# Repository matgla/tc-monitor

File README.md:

# tc-monitor

Four-channel thermocouple monitor for hand reflow with hot air and a preheater:
live temperature and graph on a 2.0" colour TFT, phase hints (preheat, soak, hot air,
liquid, cooling), peak-limit and ramp alarms, CSV over USB.

| directory | contents |
|---|---|
| `docs/design.md` | requirements, parts, RP2040 pin map, layout rules |
| `hardware/` | KiCad 10 project: schematic (5 sheets, ERC without errors); `libs/` holds the PCC-SMP footprint and the crystal symbol |
| `firmware/` | MicroPython: `reflow.py` (phase logic), `config.py`, `main.py` (still for the prototype's MAX31856/SH1106, to be ported) |
| `host/tc_plot.py` | live plot over USB, saves every run as CSV |
| `tests/` | pytest for the phase logic |

```sh
python -m pytest -q tests
uv run --with pyserial --with pyqtgraph --with PySide6 host/tc_plot.py
```

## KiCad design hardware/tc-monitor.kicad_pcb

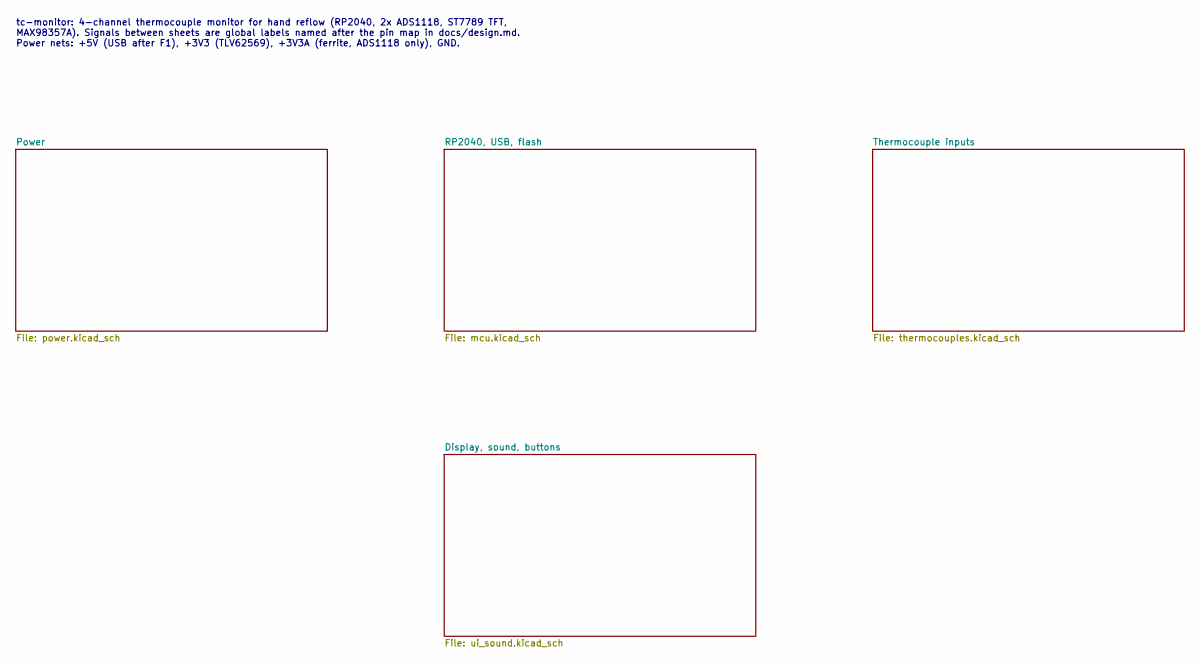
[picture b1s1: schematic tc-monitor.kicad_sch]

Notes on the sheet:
tc-monitor: 4-channel thermocouple monitor for hand reflow (RP2040, 2x ADS1118, ST7789 TFT, MAX98357A). Signals between sheets are global labels named after the pin map in docs/design.md. Power nets: +5V (USB after F1), +3V3 (TLV62569), +3V3A (ferrite, ADS1118 only), GND.

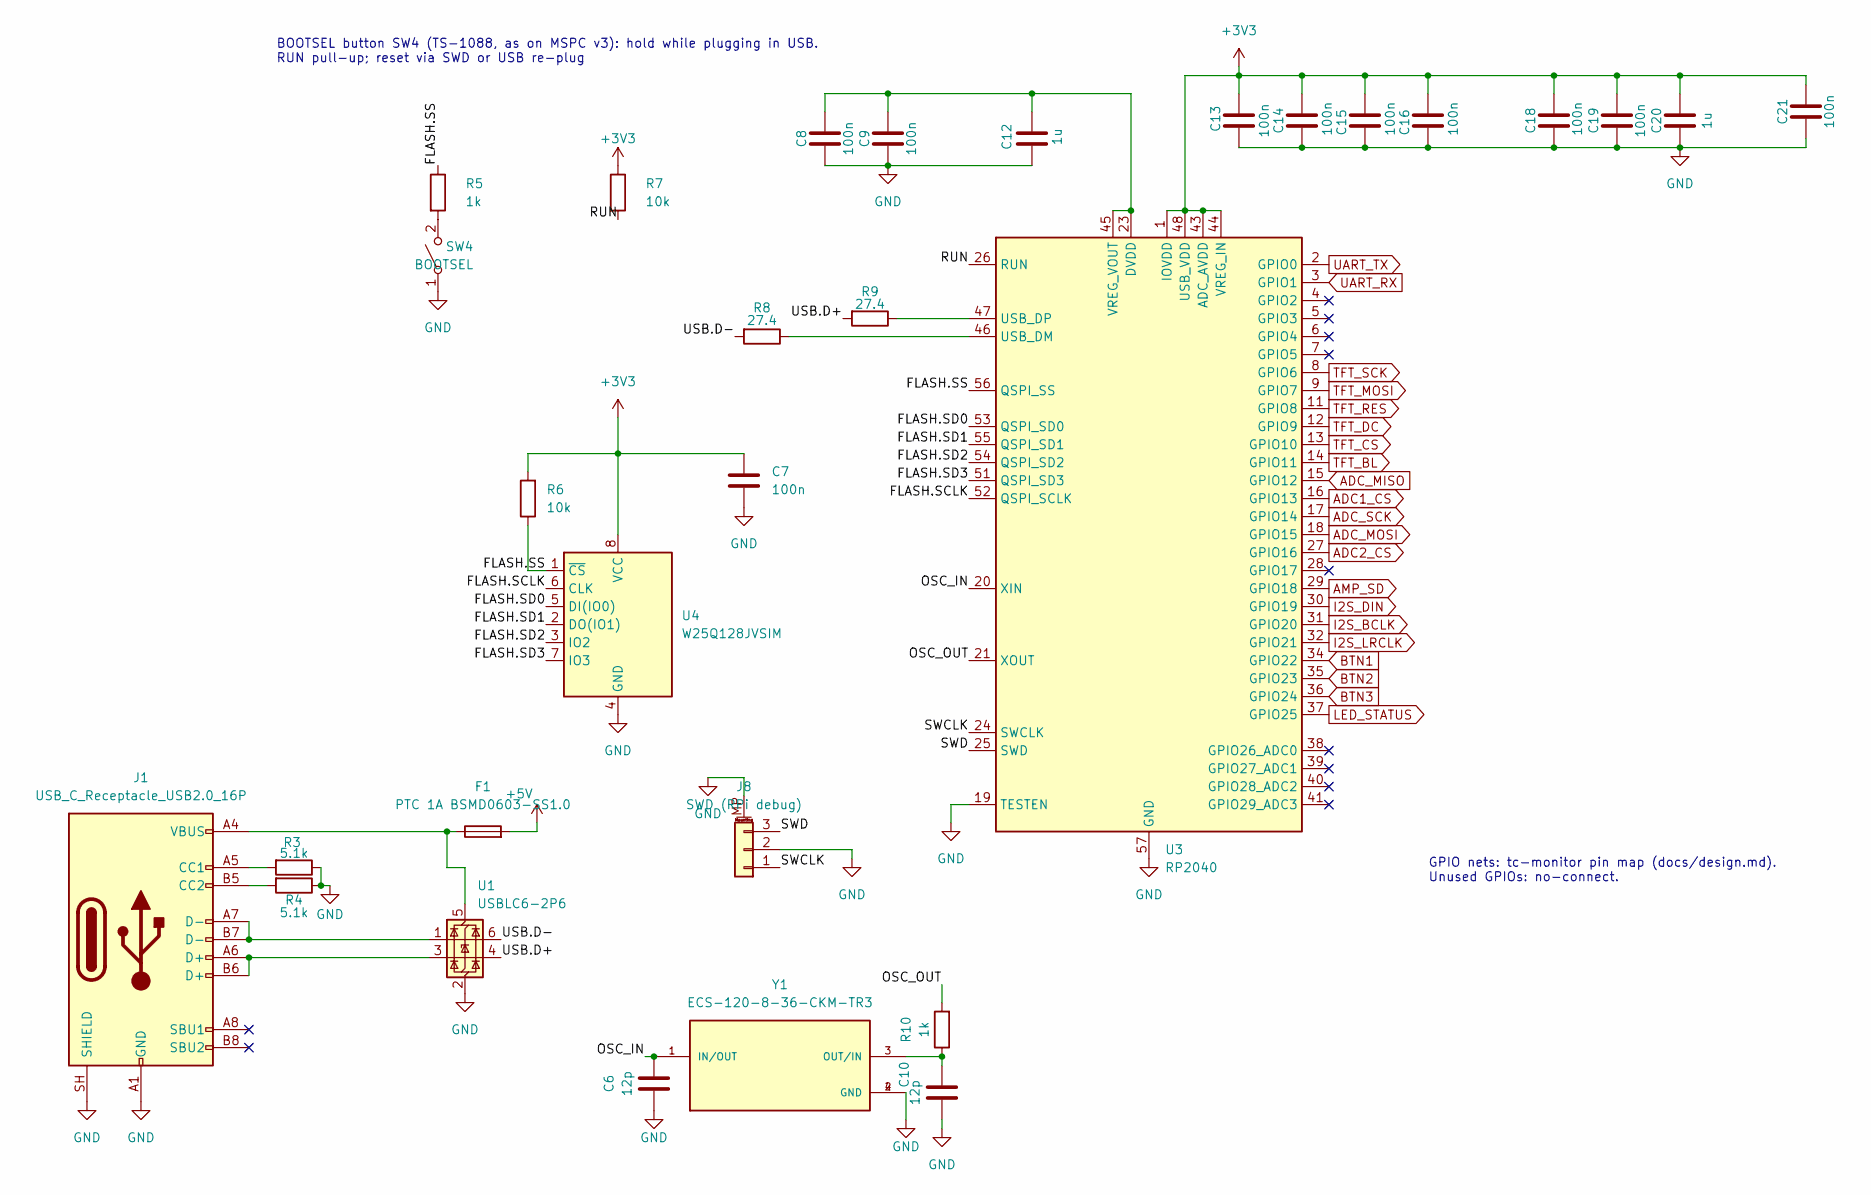
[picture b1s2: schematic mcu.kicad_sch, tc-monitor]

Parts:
C6, C10: 12p; C_0402_1005Metric_Pad0.74x0.62mm_HandSolder
C7, C8, C9, C13, C14, C15, C16, C18, C19, C21: 100n; C_0402_1005Metric_Pad0.74x0.62mm_HandSolder
C12, C20: 1u; C_0402_1005Metric_Pad0.74x0.62mm_HandSolder
F1: PTC 1A BSMD0603-SS1.0; Fuse_0603_1608Metric_Pad1.05x0.95mm_HandSolder
J1: USB_C_Receptacle_USB2.0_16P; USB_C_Receptacle_HRO_TYPE-C-31-M-12
J8: SWD (RPi debug); JST_SH_BM03B-SRSS-TB_1x03-1MP_P1.00mm_Vertical; MPN BM03B-SRSS-TB(LF)(SN); LCSC C160389
R3, R4: 5.1k; R_0402_1005Metric_Pad0.72x0.64mm_HandSolder
R5, R10: 1k; R_0402_1005Metric_Pad0.72x0.64mm_HandSolder
R6, R7: 10k; R_0402_1005Metric_Pad0.72x0.64mm_HandSolder
R8, R9: 27.4; R_0402_1005Metric_Pad0.72x0.64mm_HandSolder
SW4: BOOTSEL; SW_SPST_TS-1088-xR020; MPN TS-1088-AR02016; LCSC C720477
U1: USBLC6-2P6; SOT-666
U3: RP2040; QFN-56-1EP_7x7mm_P0.4mm_EP3.2x3.2mm_ThermalVias_D0.3
U4: W25Q128JVSIM; SOIC-8_5.3x5.3mm_P1.27mm; MPN GD25Q16EEIGR; LCSC C2986331
Y1: ECS-120-8-36-CKM-TR3; Crystal_SMD_2520-4Pin_2.5x2.0mm; PARTREV 2017; LCSC C20625731

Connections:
+3V3: C7.1, C13.1, C14.1, C15.1, C16.1, C18.1, C19.1, C20.1, C21.1, R6.2, R7.1, U3.1 (IOVDD), U3.10 (IOVDD), U3.22 (IOVDD), U3.33 (IOVDD), U3.42 (IOVDD), U3.43 (ADC_AVDD), U3.44 (VREG_IN), U3.48 (USB_VDD), U3.49 (IOVDD), U4.8 (VCC); also elsewhere on the board
+5V: F1.2; also elsewhere on the board
/RP2040, USB, flash/FLASH.SCLK: U3.52 (QSPI_SCLK), U4.6 (CLK)
/RP2040, USB, flash/FLASH.SD0: U3.53 (QSPI_SD0), U4.5 (DI(IO0))
/RP2040, USB, flash/FLASH.SD1: U3.55 (QSPI_SD1), U4.2 (DO(IO1))
/RP2040, USB, flash/FLASH.SD2: U3.54 (QSPI_SD2), U4.3 (IO2)
/RP2040, USB, flash/FLASH.SD3: U3.51 (QSPI_SD3), U4.7 (IO3)
/RP2040, USB, flash/FLASH.SS: R5.1, R6.1, U3.56 (QSPI_SS), U4.1 (~CS)
/RP2040, USB, flash/OSC_IN: C6.1, U3.20 (XIN), Y1.1 (IN/OUT)
/RP2040, USB, flash/OSC_OUT: R10.2, U3.21 (XOUT)
/RP2040, USB, flash/RUN: R7.2, U3.26 (RUN)
/RP2040, USB, flash/SWCLK: J8.1, U3.24 (SWCLK)
/RP2040, USB, flash/SWD: J8.3, U3.25 (SWD)
/RP2040, USB, flash/USB.D+: R9.2, U1.4 (I/O2)
/RP2040, USB, flash/USB.D-: R8.2, U1.6 (I/O1)
ADC1_CS: U3.16 (GPIO13); also elsewhere on the board
ADC2_CS: U3.27 (GPIO16); also elsewhere on the board
ADC_MISO: U3.15 (GPIO12); also elsewhere on the board
ADC_MOSI: U3.18 (GPIO15); also elsewhere on the board
ADC_SCK: U3.17 (GPIO14); also elsewhere on the board
AMP_SD: U3.29 (GPIO18); also elsewhere on the board
BTN1: U3.34 (GPIO22); also elsewhere on the board
BTN2: U3.35 (GPIO23); also elsewhere on the board
BTN3: U3.36 (GPIO24); also elsewhere on the board
GND: C6.2, C7.2, C8.2, C9.2, C10.2, C12.2, C13.2, C14.2, C15.2, C16.2, C18.2, C19.2, C20.2, C21.2, J1.A1 (GND), J1.A12 (GND), J1.B1 (GND), J1.B12 (GND), J1.SH (SHIELD), J8.2, J8.MP (MountPin), R3.1, R4.1, SW4.1 (A), U1.2 (GND), U3.19 (TESTEN), U3.57 (GND), U4.4 (GND), Y1.2 (GND), Y1.4 (GND); also elsewhere on the board
I2S_BCLK: U3.31 (GPIO20); also elsewhere on the board
I2S_DIN: U3.30 (GPIO19); also elsewhere on the board
I2S_LRCLK: U3.32 (GPIO21); also elsewhere on the board
LED_STATUS: U3.37 (GPIO25); also elsewhere on the board
unnamed: J1.A5 (CC1), R3.2
unnamed: J1.B5 (CC2), R4.2
unnamed: J1.A6 (D+), J1.B6 (D+), U1.3 (I/O2)
unnamed: J1.A7 (D-), J1.B7 (D-), U1.1 (I/O1)
unnamed: R5.2, SW4.2 (B)
unnamed: F1.1, J1.A4 (VBUS), J1.A9 (VBUS), J1.B4 (VBUS), J1.B9 (VBUS), U1.5 (VBUS)
unnamed: R8.1, U3.46 (USB_DM)
unnamed: R9.1, U3.47 (USB_DP)
unnamed: C8.1, C9.1, C12.1, U3.23 (DVDD), U3.45 (VREG_VOUT), U3.50 (DVDD)
unnamed: C10.1, R10.1, Y1.3 (OUT/IN)
TFT_BL: U3.14 (GPIO11); also elsewhere on the board
TFT_CS: U3.13 (GPIO10); also elsewhere on the board
TFT_DC: U3.12 (GPIO9); also elsewhere on the board
TFT_MOSI: U3.9 (GPIO7); also elsewhere on the board
TFT_RES: U3.11 (GPIO8); also elsewhere on the board
TFT_SCK: U3.8 (GPIO6); also elsewhere on the board
UART_RX: U3.3 (GPIO1); also elsewhere on the board
UART_TX: U3.2 (GPIO0); also elsewhere on the board

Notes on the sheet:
GPIO nets: tc-monitor pin map (docs/design.md). Unused GPIOs: no-connect.
BOOTSEL button SW4 (TS-1088, as on MSPC v3): hold while plugging in USB. RUN pull-up; reset via SWD or USB re-plug

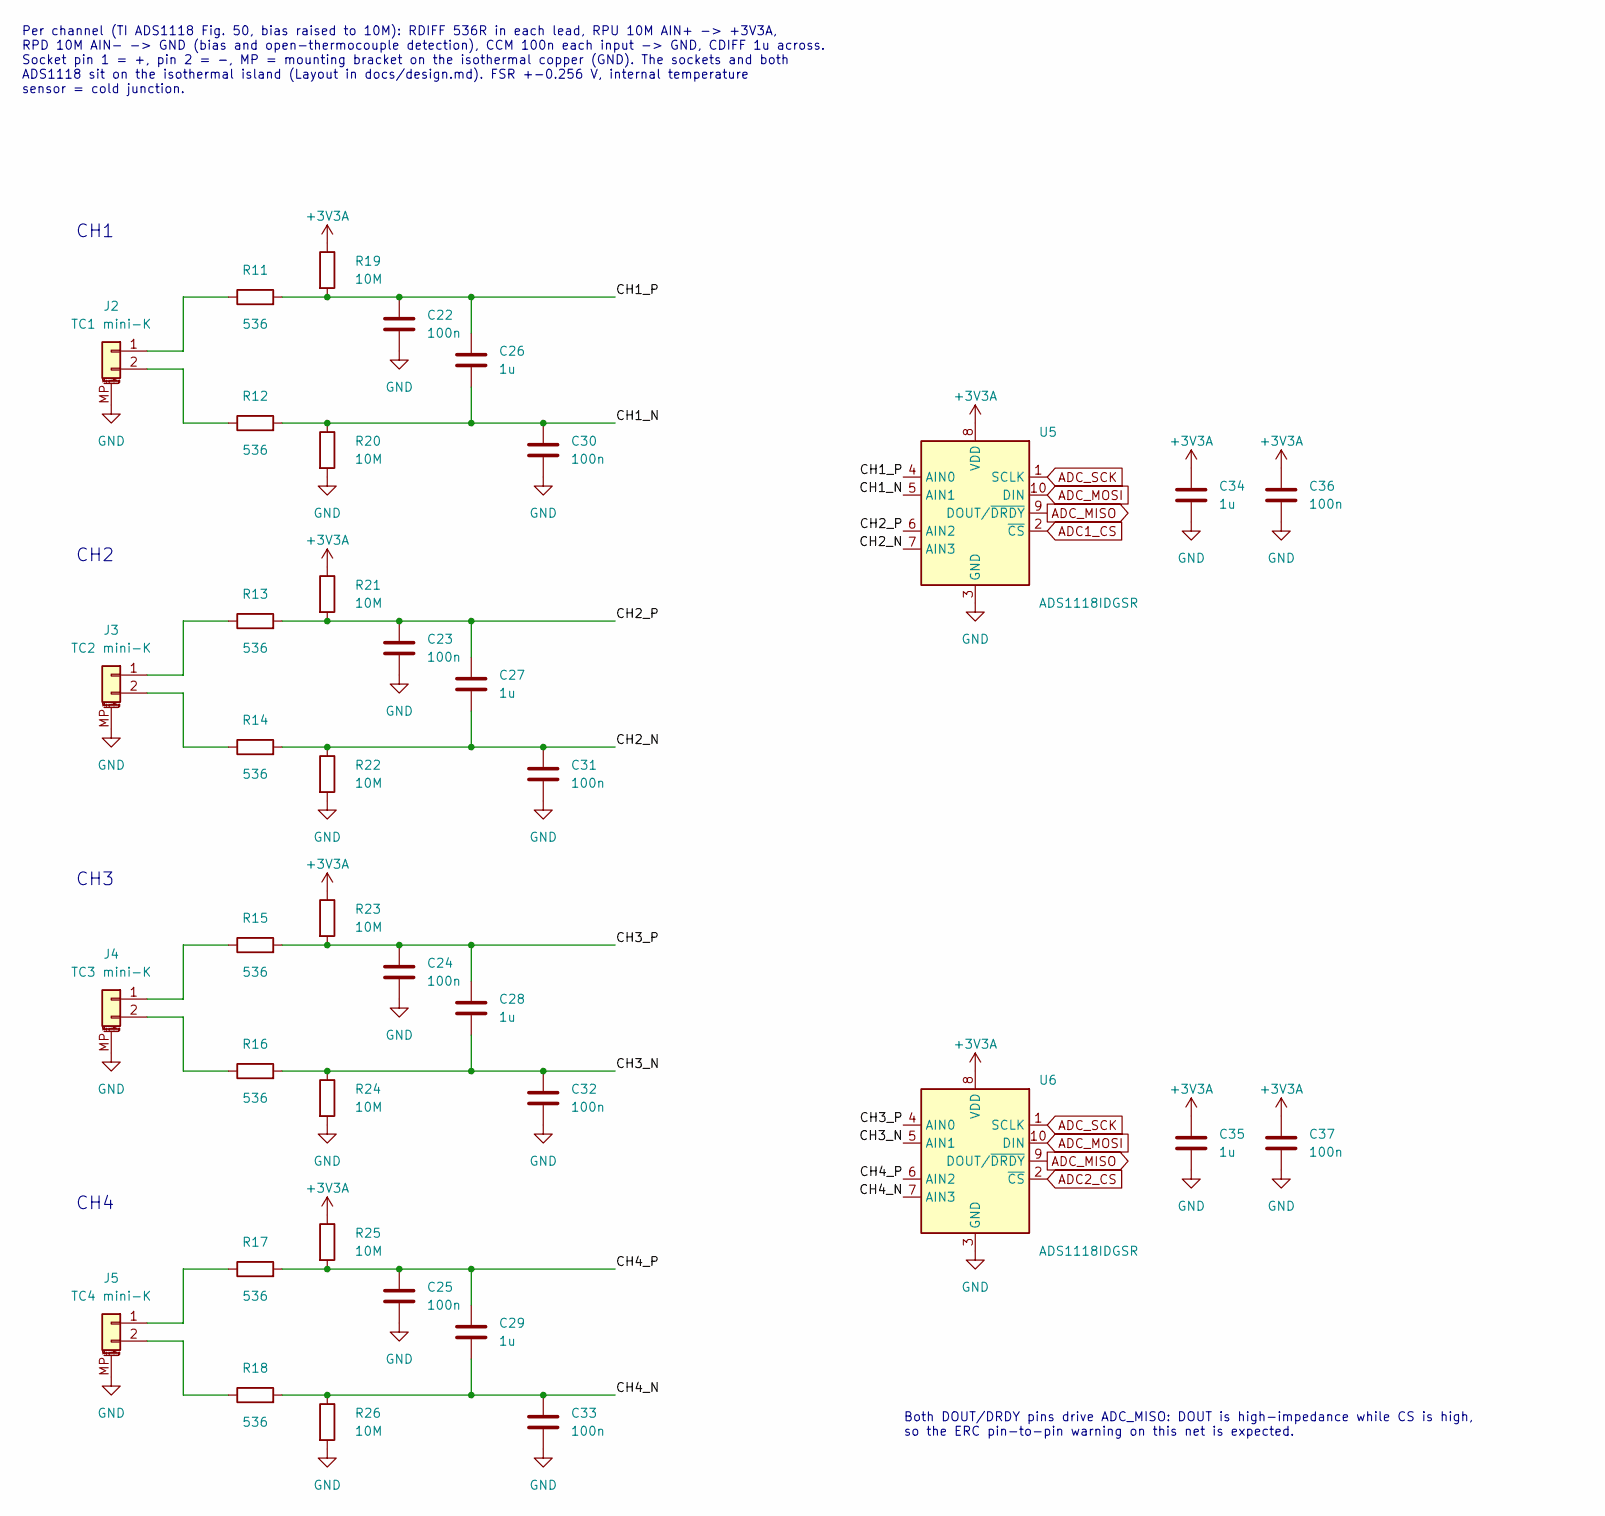
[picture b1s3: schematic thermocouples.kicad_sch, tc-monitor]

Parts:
C22, C23, C24, C25, C30, C31, C32, C33, C36, C37: 100n; C_0402_1005Metric_Pad0.74x0.62mm_HandSolder
C26, C27, C28, C29, C34, C35: 1u; C_0402_1005Metric_Pad0.74x0.62mm_HandSolder
J2: TC1 mini-K; Thermocouple_PCC-SMP_Horizontal
J3: TC2 mini-K; Thermocouple_PCC-SMP_Horizontal
J4: TC3 mini-K; Thermocouple_PCC-SMP_Horizontal
J5: TC4 mini-K; Thermocouple_PCC-SMP_Horizontal
R11, R12, R13, R14, R15, R16, R17, R18: 536; R_0402_1005Metric_Pad0.72x0.64mm_HandSolder
R19, R20, R21, R22, R23, R24, R25, R26: 10M; R_0402_1005Metric_Pad0.72x0.64mm_HandSolder
U5, U6: ADS1118IDGSR; MSOP-10_3x3mm_P0.5mm

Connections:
+3V3A: C34.1, C35.1, C36.1, C37.1, R19.1, R21.1, R23.1, R25.1, U5.8 (VDD), U6.8 (VDD); also elsewhere on the board
/Thermocouple inputs/CH1_N: C26.2, C30.1, R12.2, R20.1, U5.5 (AIN1)
/Thermocouple inputs/CH1_P: C22.1, C26.1, R11.2, R19.2, U5.4 (AIN0)
/Thermocouple inputs/CH2_N: C27.2, C31.1, R14.2, R22.1, U5.7 (AIN3)
/Thermocouple inputs/CH2_P: C23.1, C27.1, R13.2, R21.2, U5.6 (AIN2)
/Thermocouple inputs/CH3_N: C28.2, C32.1, R16.2, R24.1, U6.5 (AIN1)
/Thermocouple inputs/CH3_P: C24.1, C28.1, R15.2, R23.2, U6.4 (AIN0)
/Thermocouple inputs/CH4_N: C29.2, C33.1, R18.2, R26.1, U6.7 (AIN3)
/Thermocouple inputs/CH4_P: C25.1, C29.1, R17.2, R25.2, U6.6 (AIN2)
ADC1_CS: U5.2 (~CS); also elsewhere on the board
ADC2_CS: U6.2 (~CS); also elsewhere on the board
ADC_MISO: U5.9 (DOUT/~DRDY), U6.9 (DOUT/~DRDY); also elsewhere on the board
ADC_MOSI: U5.10 (DIN), U6.10 (DIN); also elsewhere on the board
ADC_SCK: U5.1 (SCLK), U6.1 (SCLK); also elsewhere on the board
GND: C22.2, C23.2, C24.2, C25.2, C30.2, C31.2, C32.2, C33.2, C34.2, C35.2, C36.2, C37.2, J2.MP (MountPin), J3.MP (MountPin), J4.MP (MountPin), J5.MP (MountPin), R20.2, R22.2, R24.2, R26.2, U5.3 (GND), U6.3 (GND); also elsewhere on the board
unnamed: J2.1, R11.1
unnamed: J2.2, R12.1
unnamed: J3.1, R13.1
unnamed: J3.2, R14.1
unnamed: J4.1, R15.1
unnamed: J4.2, R16.1
unnamed: J5.1, R17.1
unnamed: J5.2, R18.1

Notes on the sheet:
CH4
Per channel (TI ADS1118 Fig. 50, bias raised to 10M): RDIFF 536R in each lead, RPU 10M AIN+ -> +3V3A, RPD 10M AIN- -> GND (bias and open-thermocouple detection), CCM 100n each input -> GND, CDIFF 1u across. Socket pin 1 = +, pin 2 = -, MP = mounting bracket on the isothermal copper (GND). The socke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
CH2
CH1
Both DOUT/DRDY pins drive ADC_MISO: DOUT is high-impedance while CS is high, so the ERC pin-to-pin warning on this net is expected.
CH3

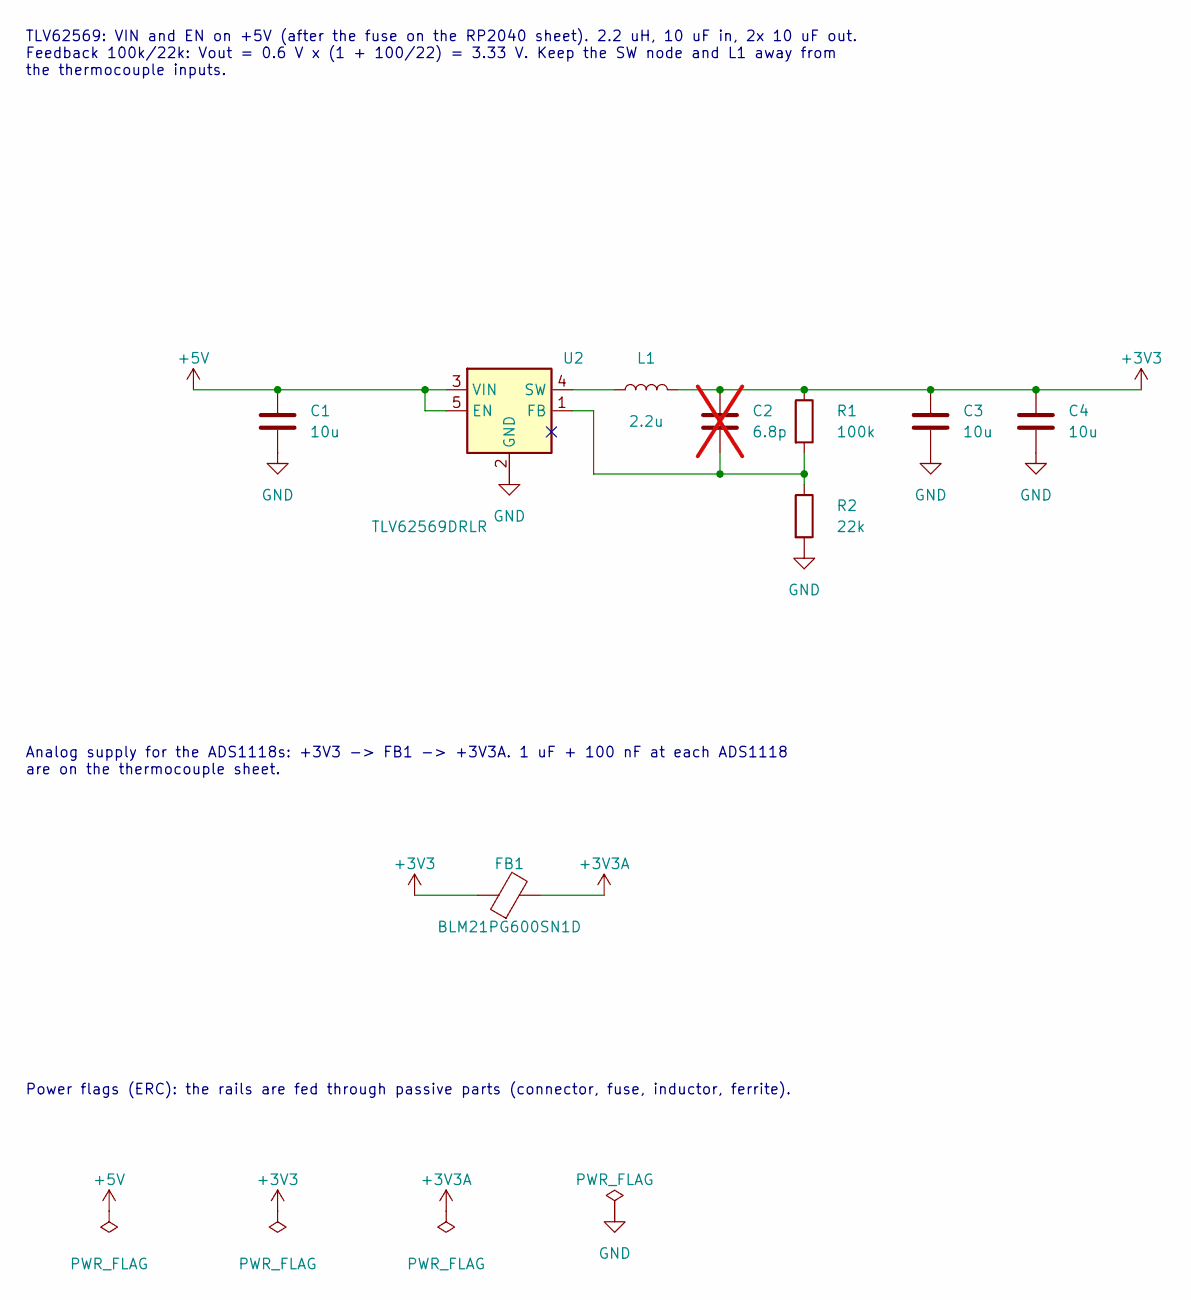
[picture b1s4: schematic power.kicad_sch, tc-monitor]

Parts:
C1: 10u; C_0603_1608Metric_Pad1.08x0.95mm_HandSolder
C2: 6.8p; C_0402_1005Metric_Pad0.74x0.62mm_HandSolder; not fitted
C3, C4: 10u; C_0402_1005Metric_Pad0.74x0.62mm_HandSolder
FB1: BLM21PG600SN1D; L_0805_2012Metric_Pad1.05x1.20mm_HandSolder
L1: 2.2u; L_0805_2012Metric_Pad1.05x1.20mm_HandSolder; MPN LQM21PN2R2NGCD
R1: 100k; R_0402_1005Metric_Pad0.72x0.64mm_HandSolder
R2: 22k; R_0402_1005Metric_Pad0.72x0.64mm_HandSolder
U2: TLV62569DRLR; SOT-563

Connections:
+3V3: C2.1, C3.1, C4.1, FB1.1, L1.2, R1.1; also elsewhere on the board
+3V3A: FB1.2; also elsewhere on the board
+5V: C1.1, U2.3 (VIN), U2.5 (EN); also elsewhere on the board
GND: C1.2, C3.2, C4.2, R2.2, U2.2 (GND); also elsewhere on the board
unnamed: C2.2, R1.2, R2.1, U2.1 (FB)
unnamed: L1.1, U2.4 (SW)

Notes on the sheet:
Power flags (ERC): the rails are fed through passive parts (connector, fuse, inductor, ferrite).
Analog supply for the ADS1118s: +3V3 -> FB1 -> +3V3A. 1 uF + 100 nF at each ADS1118 are on the thermocouple sheet.
TLV62569: VIN and EN on +5V (after the fuse on the RP2040 sheet). 2.2 uH, 10 uF in, 2x 10 uF out. Feedback 100k/22k: Vout = 0.6 V x (1 + 100/22) = 3.33 V. Keep the SW node and L1 away from the thermocouple inputs.

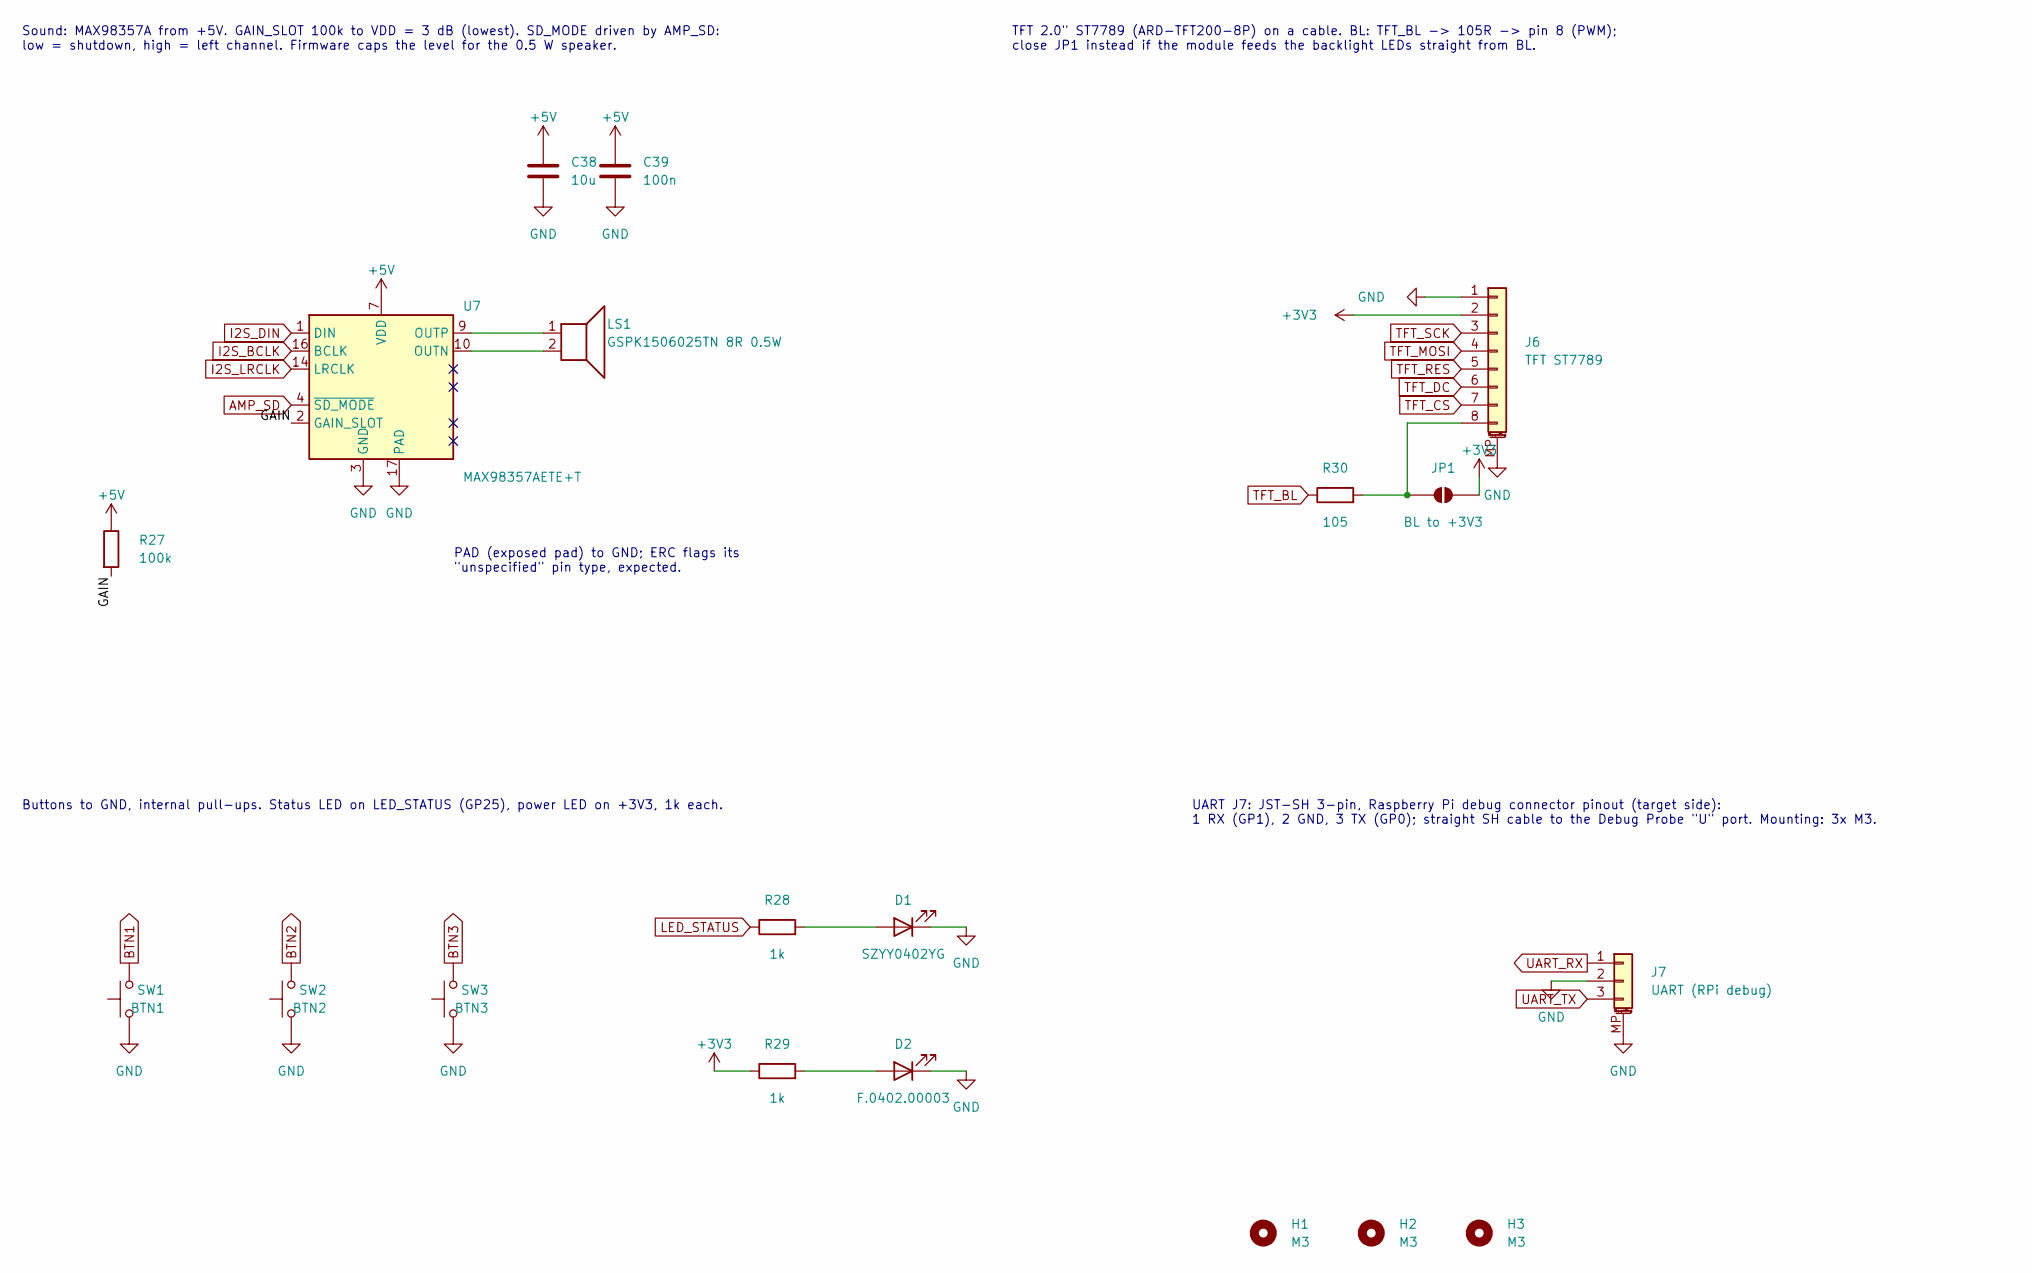
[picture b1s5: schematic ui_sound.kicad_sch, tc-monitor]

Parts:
C38: 10u; C_0603_1608Metric_Pad1.08x0.95mm_HandSolder
C39: 100n; C_0402_1005Metric_Pad0.74x0.62mm_HandSolder
D1: SZYY0402YG; LED_0402_1005Metric_Pad0.77x0.64mm_HandSolder
D2: F.0402.00003; LED_0402_1005Metric_Pad0.77x0.64mm_HandSolder
H1, H2, H3: M3; MountingHole_3.2mm_M3
J6: TFT ST7789; JST_SH_BM08B-SRSS-TB_1x08-1MP_P1.00mm_Vertical; MPN BM08B-SRSS-TB(LF)(SN); LCSC C160394
J7: UART (RPi debug); JST_SH_BM03B-SRSS-TB_1x03-1MP_P1.00mm_Vertical; MPN BM03B-SRSS-TB(LF)(SN); LCSC C160389
JP1: BL to +3V3; SolderJumper-2_P1.3mm_Open_RoundedPad1.0x1.5mm
LS1: GSPK1506025TN 8R 0.5W; Speaker_INGHAi_GSPK1506025TN_15x6mm_SpringContacts
R27: 100k; R_0402_1005Metric_Pad0.72x0.64mm_HandSolder
R28, R29: 1k; R_0402_1005Metric_Pad0.72x0.64mm_HandSolder
R30: 105; R_0402_1005Metric_Pad0.72x0.64mm_HandSolder
SW1: BTN1; SW_PUSH_6mm
SW2: BTN2; SW_PUSH_6mm
SW3: BTN3; SW_PUSH_6mm
U7: MAX98357AETE+T; TQFN-16-1EP_3x3mm_P0.5mm_EP1.23x1.23mm_ThermalVias_D0.3

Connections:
+3V3: J6.2 (Pin_2_2), JP1.2 (B), R29.1; also elsewhere on the board
+5V: C38.1, C39.1, R27.1, U7.7 (VDD), U7.8 (VDD); also elsewhere on the board
/Display, sound, buttons/GAIN: R27.2, U7.2 (GAIN_SLOT)
AMP_SD: U7.4 (~SD_MODE); also elsewhere on the board
BTN1: SW1.2; also elsewhere on the board
BTN2: SW2.2; also elsewhere on the board
BTN3: SW3.2; also elsewhere on the board
GND: C38.2, C39.2, D1.1 (K), D2.1 (K), J6.1 (Pin_1_1), J6.MP (MountPin), J7.2, J7.MP (MountPin), SW1.1, SW2.1, SW3.1, U7.3 (GND), U7.11 (GND), U7.15 (GND), U7.17 (PAD); also elsewhere on the board
I2S_BCLK: U7.16 (BCLK); also elsewhere on the board
I2S_DIN: U7.1 (DIN); also elsewhere on the board
I2S_LRCLK: U7.14 (LRCLK); also elsewhere on the board
LED_STATUS: R28.1; also elsewhere on the board
unnamed: D1.2 (A), R28.2
unnamed: D2.2 (A), R29.2
unnamed: J6.8 (Pin_8_8), JP1.1 (A), R30.2
unnamed: LS1.2, U7.10 (OUTN)
unnamed: LS1.1, U7.9 (OUTP)
TFT_BL: R30.1; also elsewhere on the board
TFT_CS: J6.7 (Pin_7_7); also elsewhere on the board
TFT_DC: J6.6 (Pin_6_6); also elsewhere on the board
TFT_MOSI: J6.4 (Pin_4_4); also elsewhere on the board
TFT_RES: J6.5 (Pin_5_5); also elsewhere on the board
TFT_SCK: J6.3 (Pin_3_3); also elsewhere on the board
UART_RX: J7.1; also elsewhere on the board
UART_TX: J7.3; also elsewhere on the board

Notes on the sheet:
PAD (exposed pad) to GND; ERC flags its "unspecified" pin type, expected.
TFT 2.0" ST7789 (ARD-TFT200-8P) on a cable. BL: TFT_BL -> 105R -> pin 8 (PWM); close JP1 instead if the module feeds the backlight LEDs straight from BL.
Sound: MAX98357A from +5V. GAIN_SLOT 100k to VDD = 3 dB (lowest). SD_MODE driven by AMP_SD: low = shutdown, high = left channel. Firmware caps the level for the 0.5 W speaker.
Buttons to GND, internal pull-ups. Status LED on LED_STATUS (GP25), power LED on +3V3, 1k each.
UART J7: JST-SH 3-pin, Raspberry Pi debug connector pinout (target side): 1 RX (GP1), 2 GND, 3 TX (GP0); straight SH cable to the Debug Probe "U" port. Mounting: 3x M3.

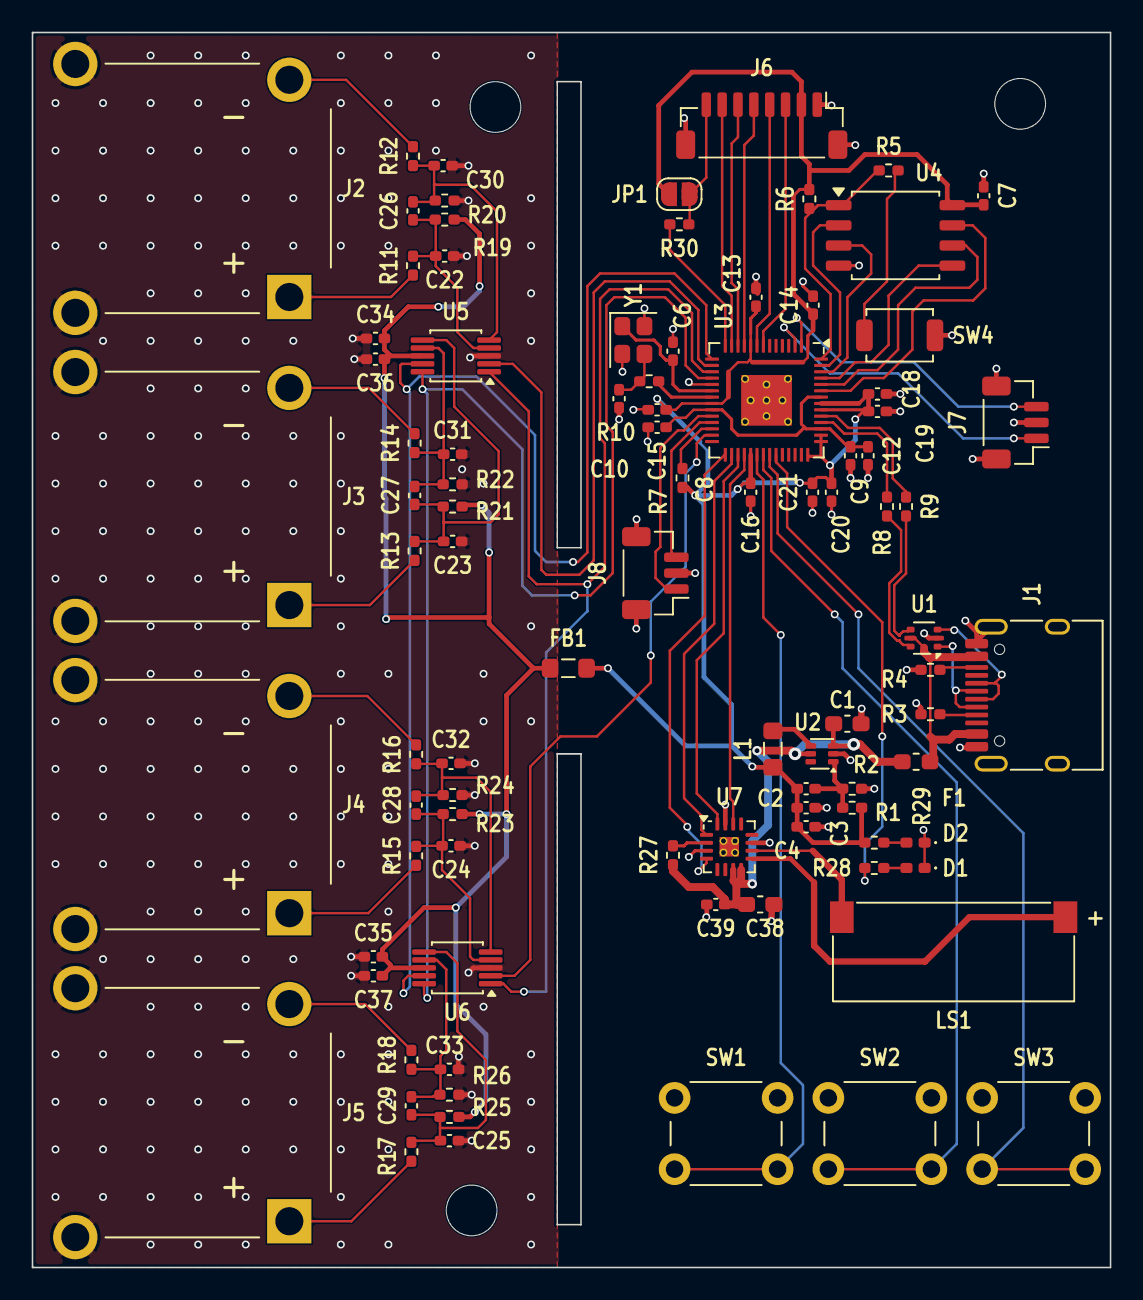
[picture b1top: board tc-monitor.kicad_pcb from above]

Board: 4 copper layers, 68.0 x 77.9 mm, 96 parts (0 on the bottom side), 72 nets.

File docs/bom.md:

# BOM: one board

Storage stock from the ESU inventory cache (synced 2026-11-10); LCSC stock and prices
read 2026-11-11. Counts match the schematic draft in `hardware/` (BOM export 2026-11-11);
RP2040 decoupling follows the minimal design: one 100 nF per IOVDD, USB_VDD and ADC_AVDD
pin (8), one per DVDD pin (2), 1 µF on VREG_IN and on VREG_VOUT, plus 100 nF on the flash
(the extra DVDD cap, the VBUS cap and the TFT-header cap were removed on 2026-11-12). Every storage line covers the quantity needed. "Order" includes spares
for rework practice.

## Shopping list

### Now (needed for footprints, enclosure and testing)

| Item | Qty | Where | Notes |
|---|---|---|---|
| Miniature type-K PCB socket, horizontal, PCC-SMP-CV-K (Omega PCC-SMP clone, K-alloy contacts) | 5 (4 + 1 spare) | AliExpress, 46.49 zł per 5 | plug enters parallel to the board, through the enclosure wall at the board edge. Footprint from the PCC-SMP drawing (4 holes ø1.77 mm: contact legs 13.7 mm apart, bracket legs 15.7 mm; the plug blades are 7.9 mm apart); measure one on arrival before the PCB order. Fallback: RS PRO 381-7564 / Labfacility IM-K-PCB (different footprint) |
| TFT 2.0" 240×320 ST7789V, SPI 8-pin, ARD-TFT200-8P | 1 | Allegro | 58 × 37 mm. On arrival, measure the BL pin current and the mounting holes. Any ST7789 240×320 module with the same 8 pins fits |
| Type-K thermocouple, thin wire, exposed junction, miniature plug | 2 (board + package; channels 3–4 later) | Allegro, BGA-station type: PFA, 0.25 mm wire, 0.8 mm bead, 1 m, ±2.5 °C / 0.75 %, yellow ANSI mini plug | insulation rated 300 °C: keep the lead out of the hot-air jet and wrap the first 2–3 cm at the bead in Kapton. Mini plug fits the IEC socket (same pins, only colour differs). Omega 5SRTC-GG-K-30-36 (glass fibre) dropped at about $100 per 5 |
| LCR tweezers meter (R 10 mΩ–10 MΩ, C 1 pF–22 mF, L 1 µH–10 H, own calibration) | 1 | about 100 zł | external tool for R, C, L and diodes; not part of the board |

### With the board (after the layout)

Separate LCSC order (it does not ship with JLCPCB). Keep it under €150: LCSC then
charges the 23 % Polish VAT at checkout (IOSS); check the checkout for any EU small-parcel
duty. Above €150 the courier adds duty and a clearance fee. The same parts from DigiKey PL
cost about 210 zł net (ADS1118 21.30 zł each) (checked 2026-11-11).

| Ref | Part | LCSC | Qty | Order | Unit price | Line |
|---|---|---|---|---|---|---|
| U5, U6 | ADS1118IDGSR, VSSOP-10 | [C55347](https://www.lcsc.com/product-detail/C55347.html) | 2 | 4 | $1.73 | $6.93 |
| R | 10 MΩ 1 % 0402, 0402WGF1005TCE (thermocouple bias) | [C26082](https://www.lcsc.com/product-detail/C26082.html) | 8 | 100 (min.) | $0.0012 | $0.12 |
| U7 | MAX98357AETE+T, I2S amplifier, TQFN-16 3×3 | [C910544](https://www.lcsc.com/product-detail/C910544.html) | 1 | 3 | $1.32 | $3.96 |
| LS1 | INGHAi GSPK1506025TN-8R0.5W-1, 8 Ω 0.5 W, 15×6×2.5 mm, spring contacts (pressure mount) | [C46961944](https://www.lcsc.com/product-detail/C46961944.html) | 1 | 2 | $0.80 | $1.61 |
| J6 | JST SH 8-pin header, vertical, BM08B-SRSS-TB(LF)(SN) (TFT) | [C160394](https://www.lcsc.com/product-detail/C160394.html) | 1 | 2 | $0.44 | $0.88 |
| J7, J8 | JST SH 3-pin header, vertical, BM03B-SRSS-TB(LF)(SN) (UART and SWD, Raspberry Pi debug connector) | [C160389](https://www.lcsc.com/product-detail/C160389.html) | 2 | 5 (min.) | $0.28 | $1.39 |

LCSC total about $14.90 plus shipping.

| Item | Qty | Where |
|---|---|---|
| PCB, 4 layers JLC04161H-3313, 1.6 mm, 68 × 77.9 mm, ENIG, with stencil | 5 | [JLCPCB](https://jlcpcb.com) |

### Consumables not tracked in storage (check the workshop)

Lead-free paste SAC305, flux, Kapton tape, aluminium tape (for the thermocouple beads
under IR).

## Full BOM

**storage** = take from storage (code, stock); **ORDER** = in the shopping list above.

| Ref | Part | Qty | Source | Code | Stock |
|---|---|---|---|---|---|
| U1 | USBLC6-2P6, SOT-666 | 1 | storage | `USBLC6-2P6` | 9 |
| U2 | TLV62569DRLR buck, SOT-563 | 1 | storage | `TLV62569DRLR` | 9 |
| U3 | RP2040, QFN-56 | 1 | storage | `RP2040` | 12 |
| U4 | W25Q128JVSIM, SOIC-8 208 mil | 1 | storage | `W25Q128JVSIM` | 10 |
| U5, U6 | ADS1118IDGSR, VSSOP-10 | 2 | **ORDER** LCSC | C55347 | |
| U7 | MAX98357AETE+T, TQFN-16 | 1 | **ORDER** LCSC | C910544 | |
| D1 | LED 0402 yellow-green (status) | 1 | storage | `SZYY0402YG` | 50 |
| D2 | LED 0402 red (power) | 1 | storage | `F.0402.00003` | 100 |
| L1 | 2.2 µH LQM21PN2R2NGCD, 0805 | 1 | storage | `LQM21PN2R2NGCD` | 19 |
| FB1 | ferrite BLM21PG600SN1D, 0805 | 1 | storage | `BLM21PG600SN1D` | 28 |
| F1 | PTC 1 A BSMD0603-SS1.0 | 1 | storage | `BSMD0603-SS1.0` | 20 |
| Y1 | 12 MHz ECS-120-8-36-CKM-TR3, 2.5×2.0 | 1 | storage | `ECS-120-8-36-CKM-TR3` | 29 |
| LS1 | speaker INGHAi GSPK1506025TN, 8 Ω 0.5 W, spring contacts | 1 | **ORDER** LCSC | C46961944 | |
| SW1–SW3 | tact switch 6×6 THT (user buttons) | 3 | storage | `TCTSW66` | 41 |
| SW4 | tactile switch 4×3 mm SMD, TS-1088-AR02016 (BOOTSEL, as on MSPC v3) | 1 | storage | `TS-1088-AR02016` | 20 |
| J1 | USB-C 16-pin, HRO TYPE-C-31-M-12 (as on MSPC v3) | 1 | storage | `USB-C16PINH` | 10 |
| J2–J5 | miniature type-K PCB socket PCC-SMP-CV-K (horizontal) | 4 | **ORDER** AliExpress | | |
| J8 | JST SH 3-pin BM03B-SRSS-TB (SWD) | 1 | **ORDER** LCSC | C160389 | |
| J6 | JST SH 8-pin header BM08B-SRSS-TB (TFT) | 1 | **ORDER** LCSC | C160394 | |
| J7 | JST SH 3-pin BM03B-SRSS-TB (UART) | 1 | **ORDER** LCSC | C160389 | |
| — | TFT module 2.0" ST7789V, ARD-TFT200-8P | 1 | **ORDER** | | |
| — | TFT cable: ready-made JST SH 1.0 mm 8-pin cable (pre-crimped, about 15 cm), one end cut off and soldered straight to the module pads | 1 | **ORDER** AliExpress | | |
| R | 105 Ω 0402 (TFT backlight series) | 1 | storage | `RC0402FR-07105RL` | 99 |
| JP1 | solder jumper (BL to +3V3), PCB only | — | — | | |
| R | 5.1 kΩ 0402 (USB CC) | 2 | storage | `RC0402FR-075K1L` | 48 |
| R | 27.4 Ω 0402 (USB D±) | 2 | storage | `RC0402FR-0727R4L` | 96 |
| R | 1 kΩ 0402 (XOUT, BOOTSEL, LEDs) | 4 | storage | `RC0402FR-071KL` | 95 |
| R | 10 kΩ 0402 (RUN, flash CS pull-ups) | 2 | storage | `RC0402FR-0710KL` | 83 |
| R | 100 kΩ 0402 (buck feedback top, amplifier GAIN to VDD) | 2 | storage | `RC0402FR-07100KL` | 97 |
| R | 22 kΩ 0402 (buck feedback bottom, 3.33 V) | 1 | storage | `RC0402FR-0722KL` | 98 |
| R | 536 Ω 0402 (thermocouple filter) | 8 | storage | `RC0402FR-07536RL` | 97 |
| R | 10 MΩ 0402 (thermocouple bias) | 8 | **ORDER** LCSC | C26082 | |
| C | 100 nF 0402 (decoupling, common-mode filter) | 22 | storage | `CC0402KRX7R6BB104` | 190 |
| C | 1 µF 0402 (VREG, differential filter, analog) | 8 | storage | `GRM155R61E105KA12D` | 118 |
| C | 10 µF 0402 (2× buck out) | 2 | storage | `CL05A106MP5NUNC` | 49 |
| C | 10 µF 0603 16 V X6S, CL10X106MO8NRNC (buck in, amplifier) | 2 | storage | `CC60310u` | 8 |
| C | 12 pF 0402 C0G (crystal) | 2 | storage | `UMK105CG120JVHF` | 23 |
| C | 6.8 pF 0402 (buck feed-forward, DNP footprint) | 0 (1) | storage | `CC4026p8` | 299 |
| — | M3 screws for mounting | 3 | storage | `M3x10P` | 14 |

Notes:

- 536 Ω instead of TI's 499 Ω only moves the thermocouple filter corner from 160 Hz to
  150 Hz.
- The buck feedback 100k/22k gives 3.33 V.
